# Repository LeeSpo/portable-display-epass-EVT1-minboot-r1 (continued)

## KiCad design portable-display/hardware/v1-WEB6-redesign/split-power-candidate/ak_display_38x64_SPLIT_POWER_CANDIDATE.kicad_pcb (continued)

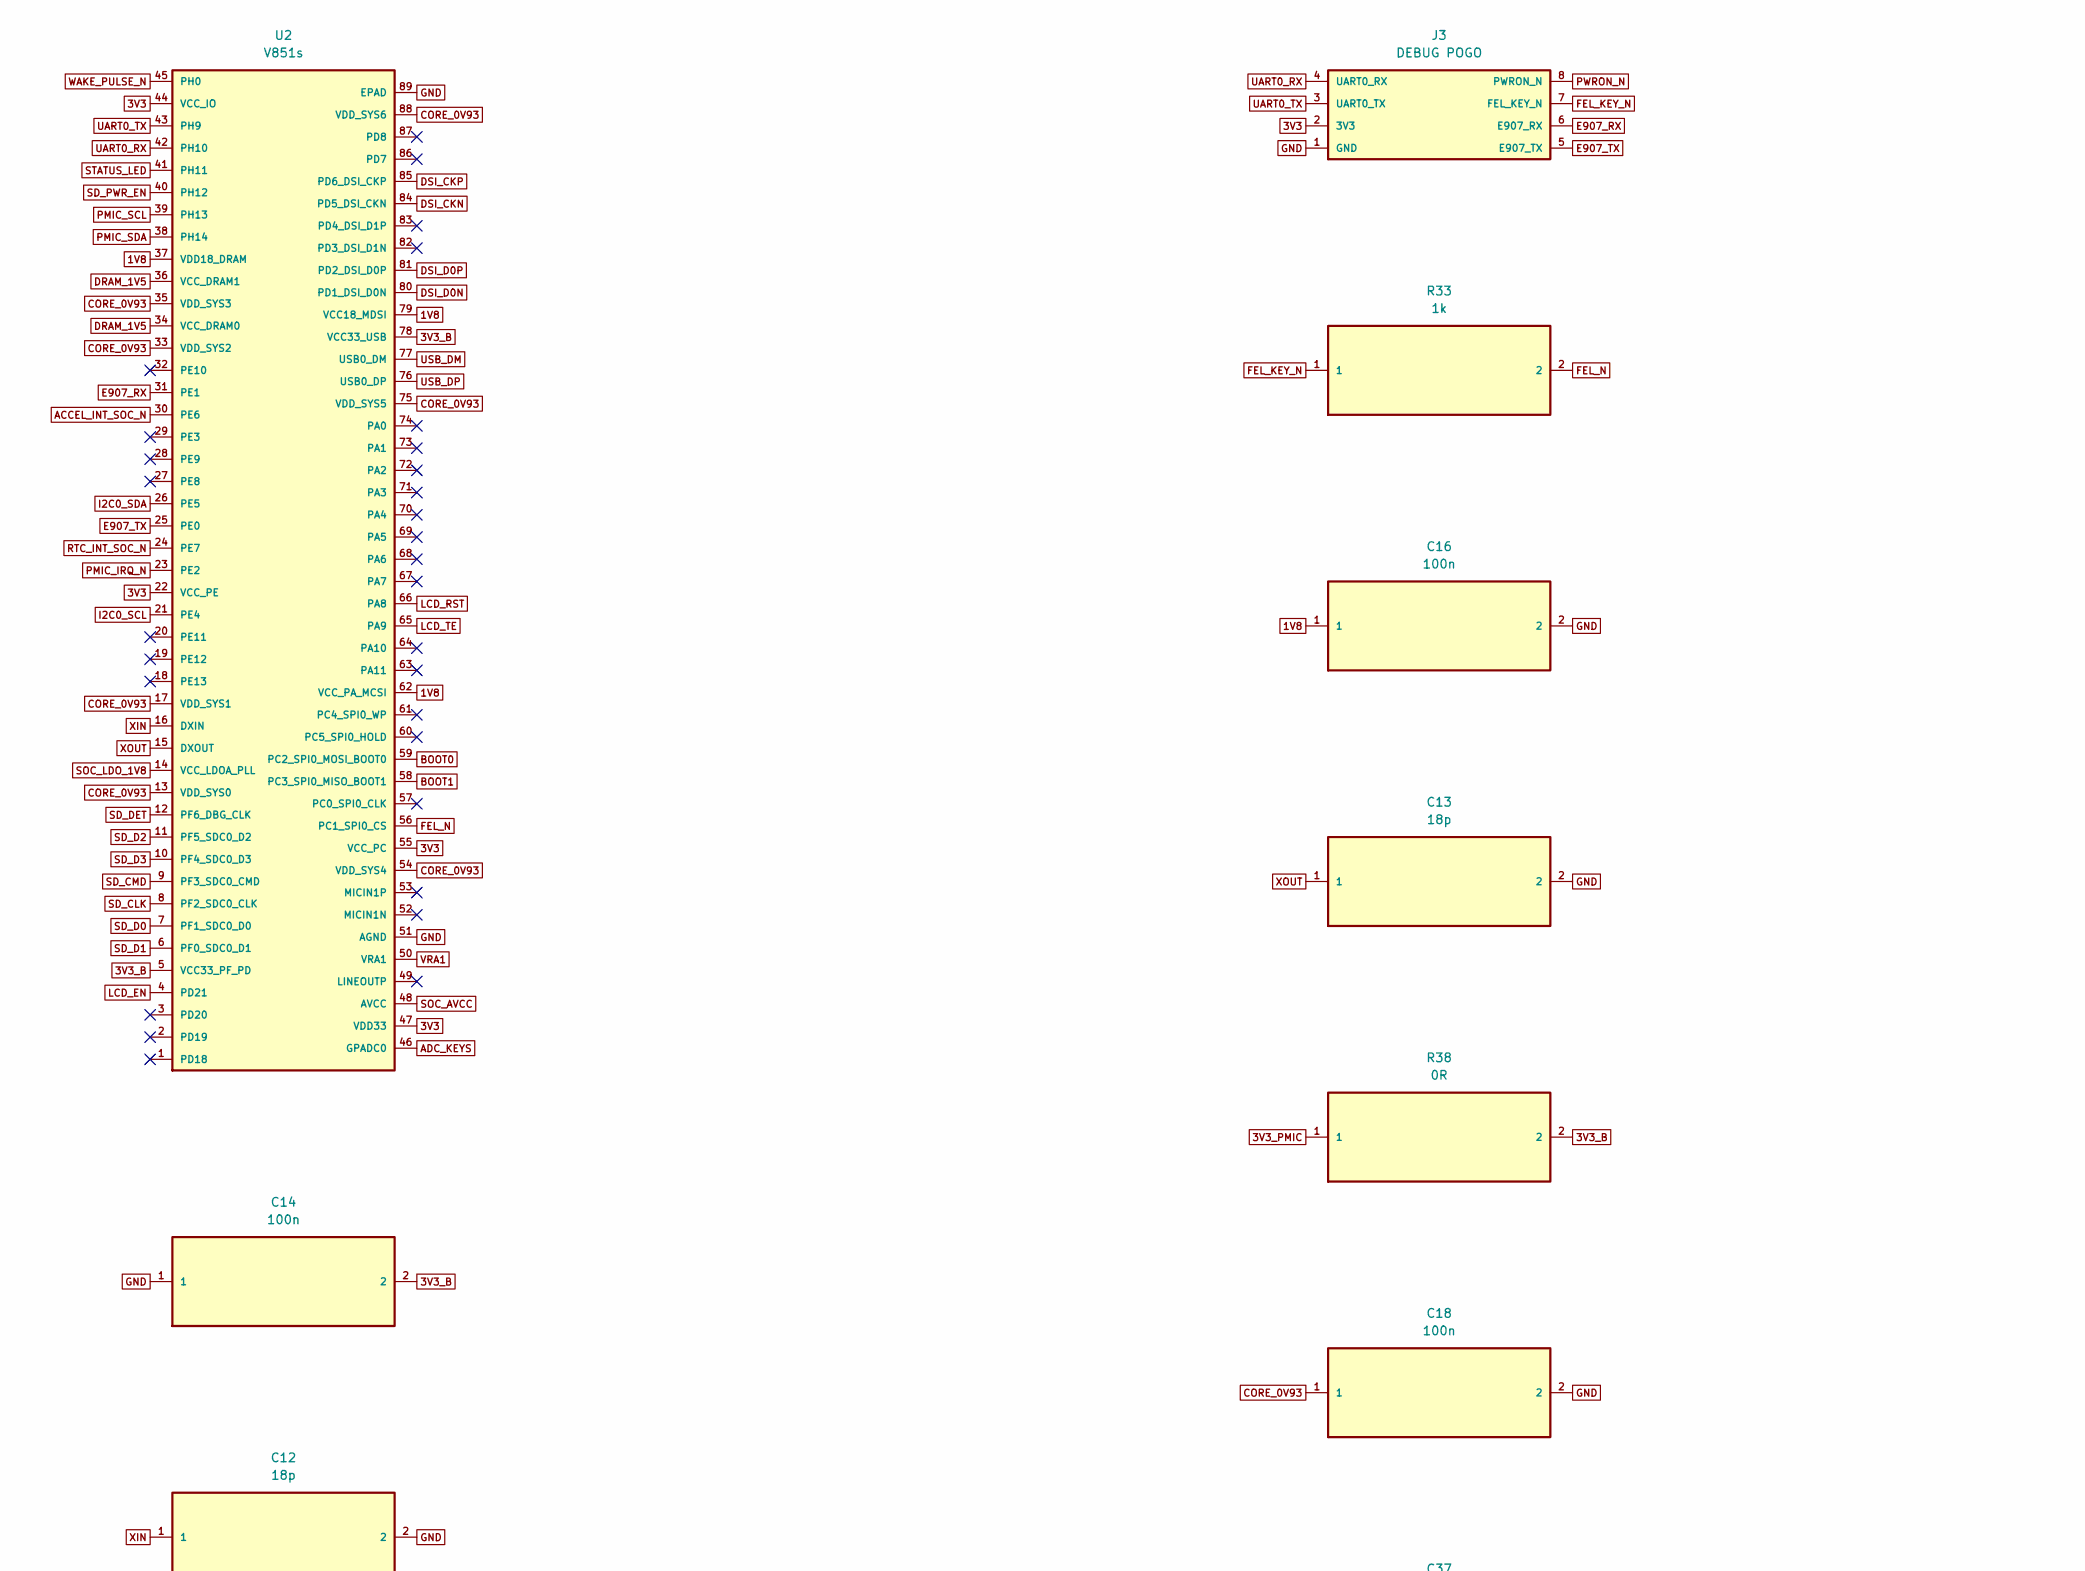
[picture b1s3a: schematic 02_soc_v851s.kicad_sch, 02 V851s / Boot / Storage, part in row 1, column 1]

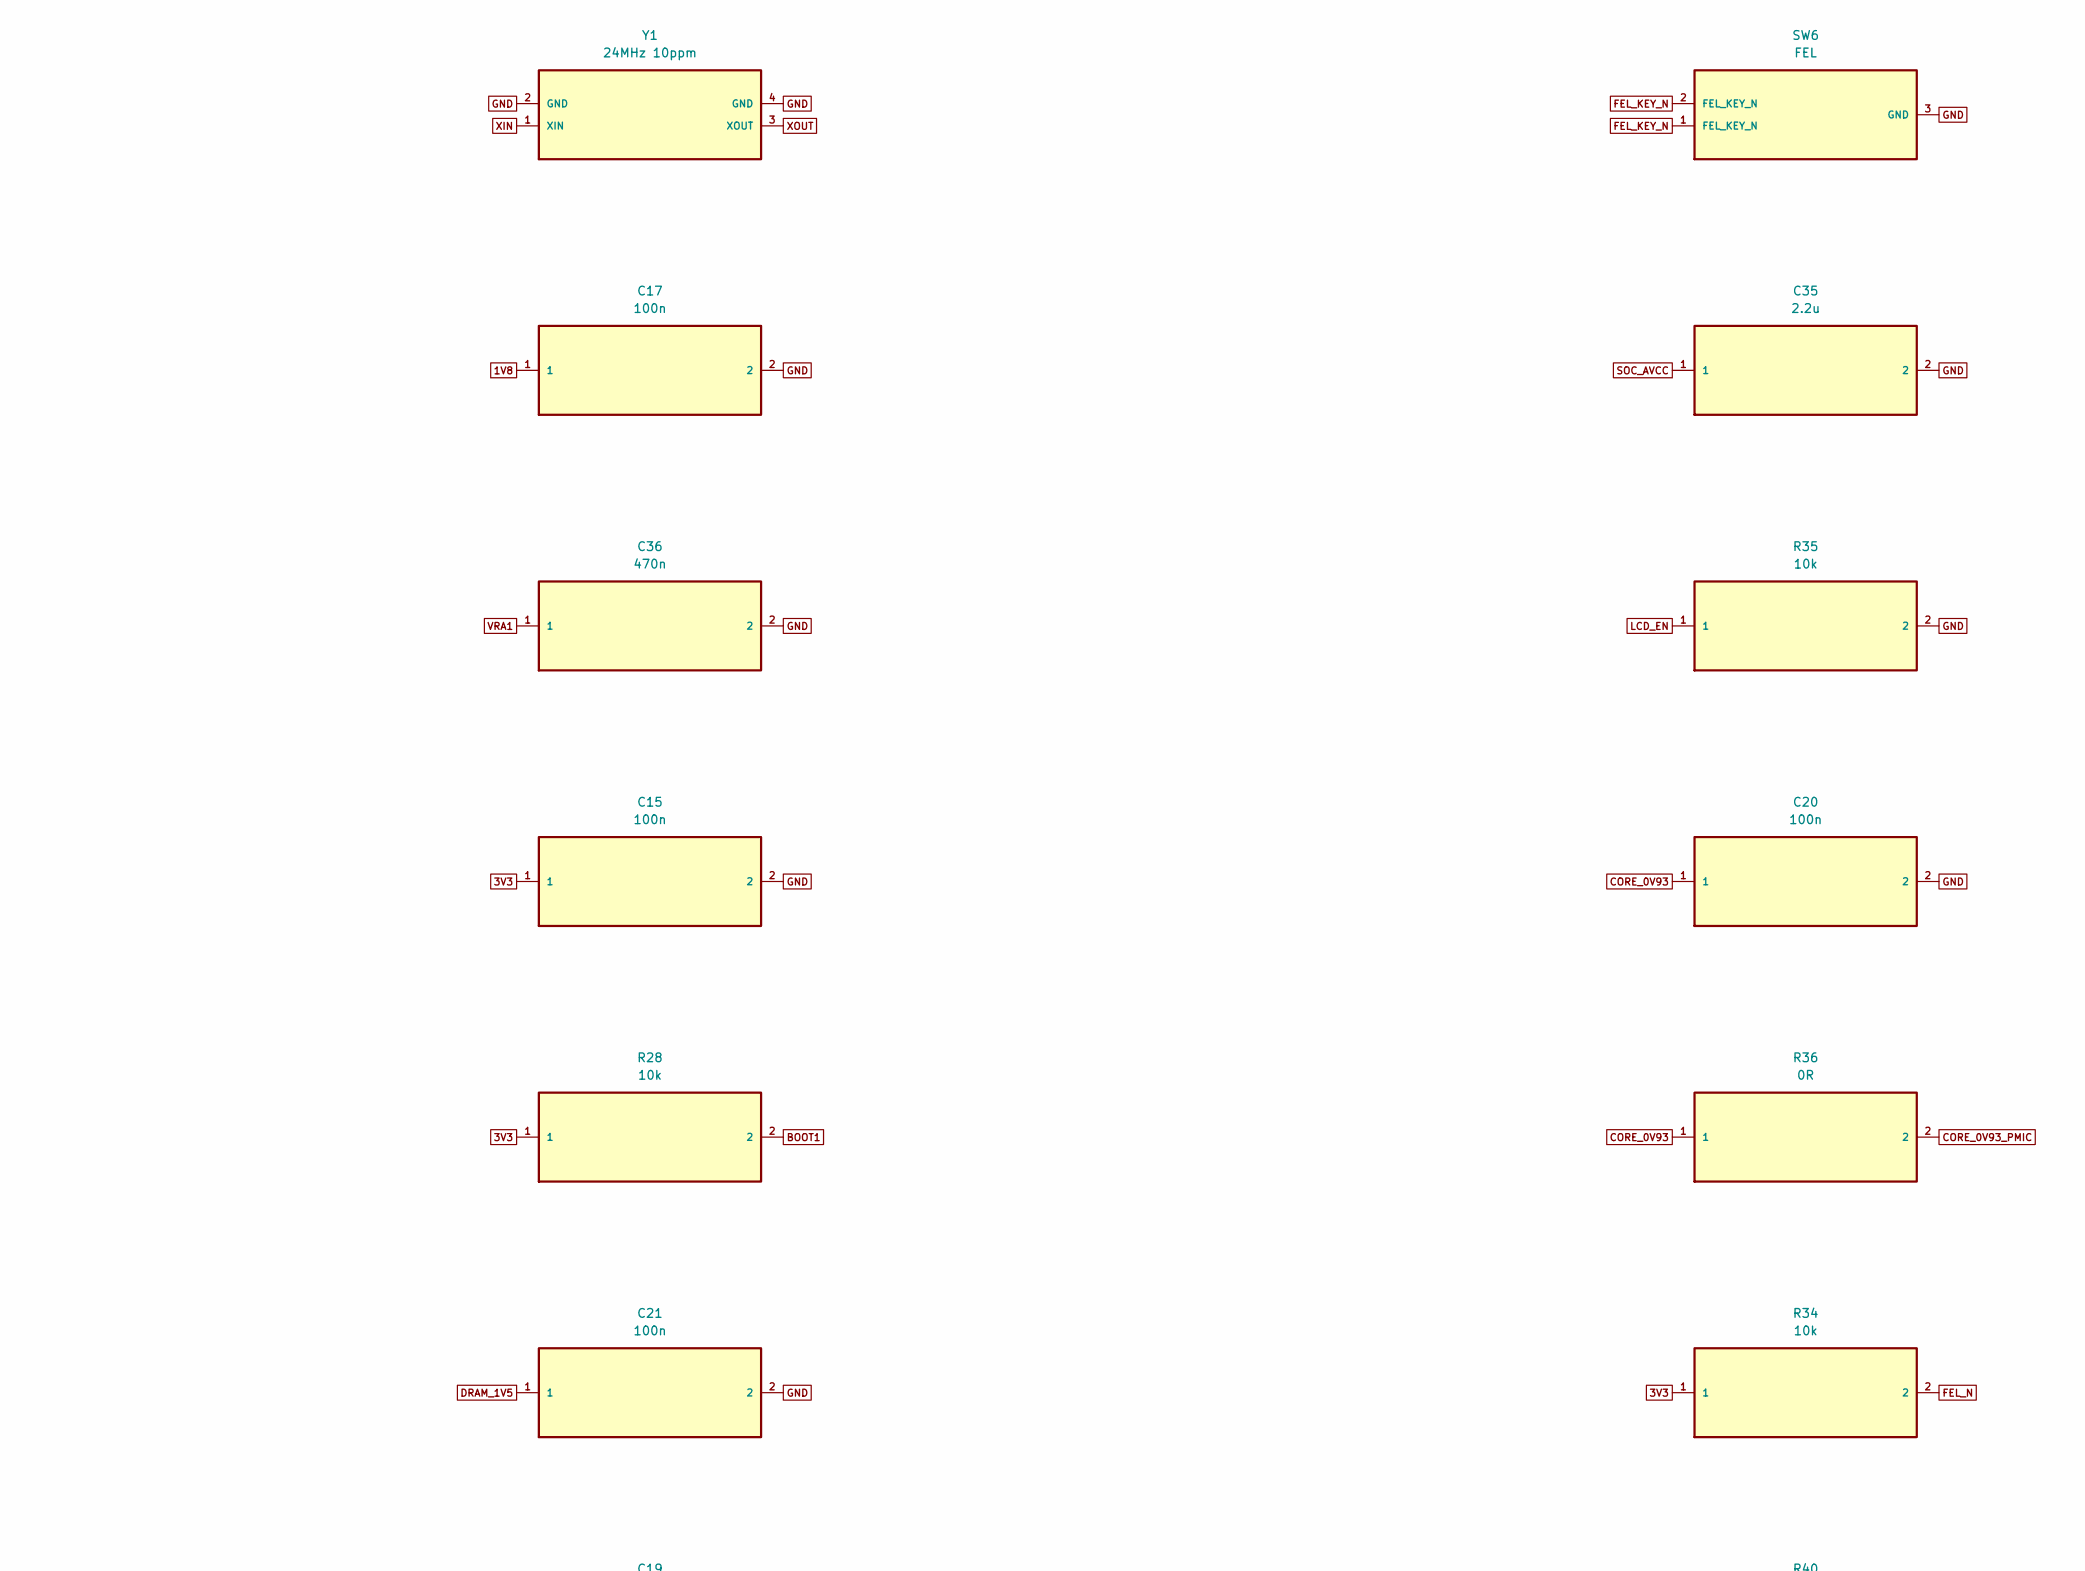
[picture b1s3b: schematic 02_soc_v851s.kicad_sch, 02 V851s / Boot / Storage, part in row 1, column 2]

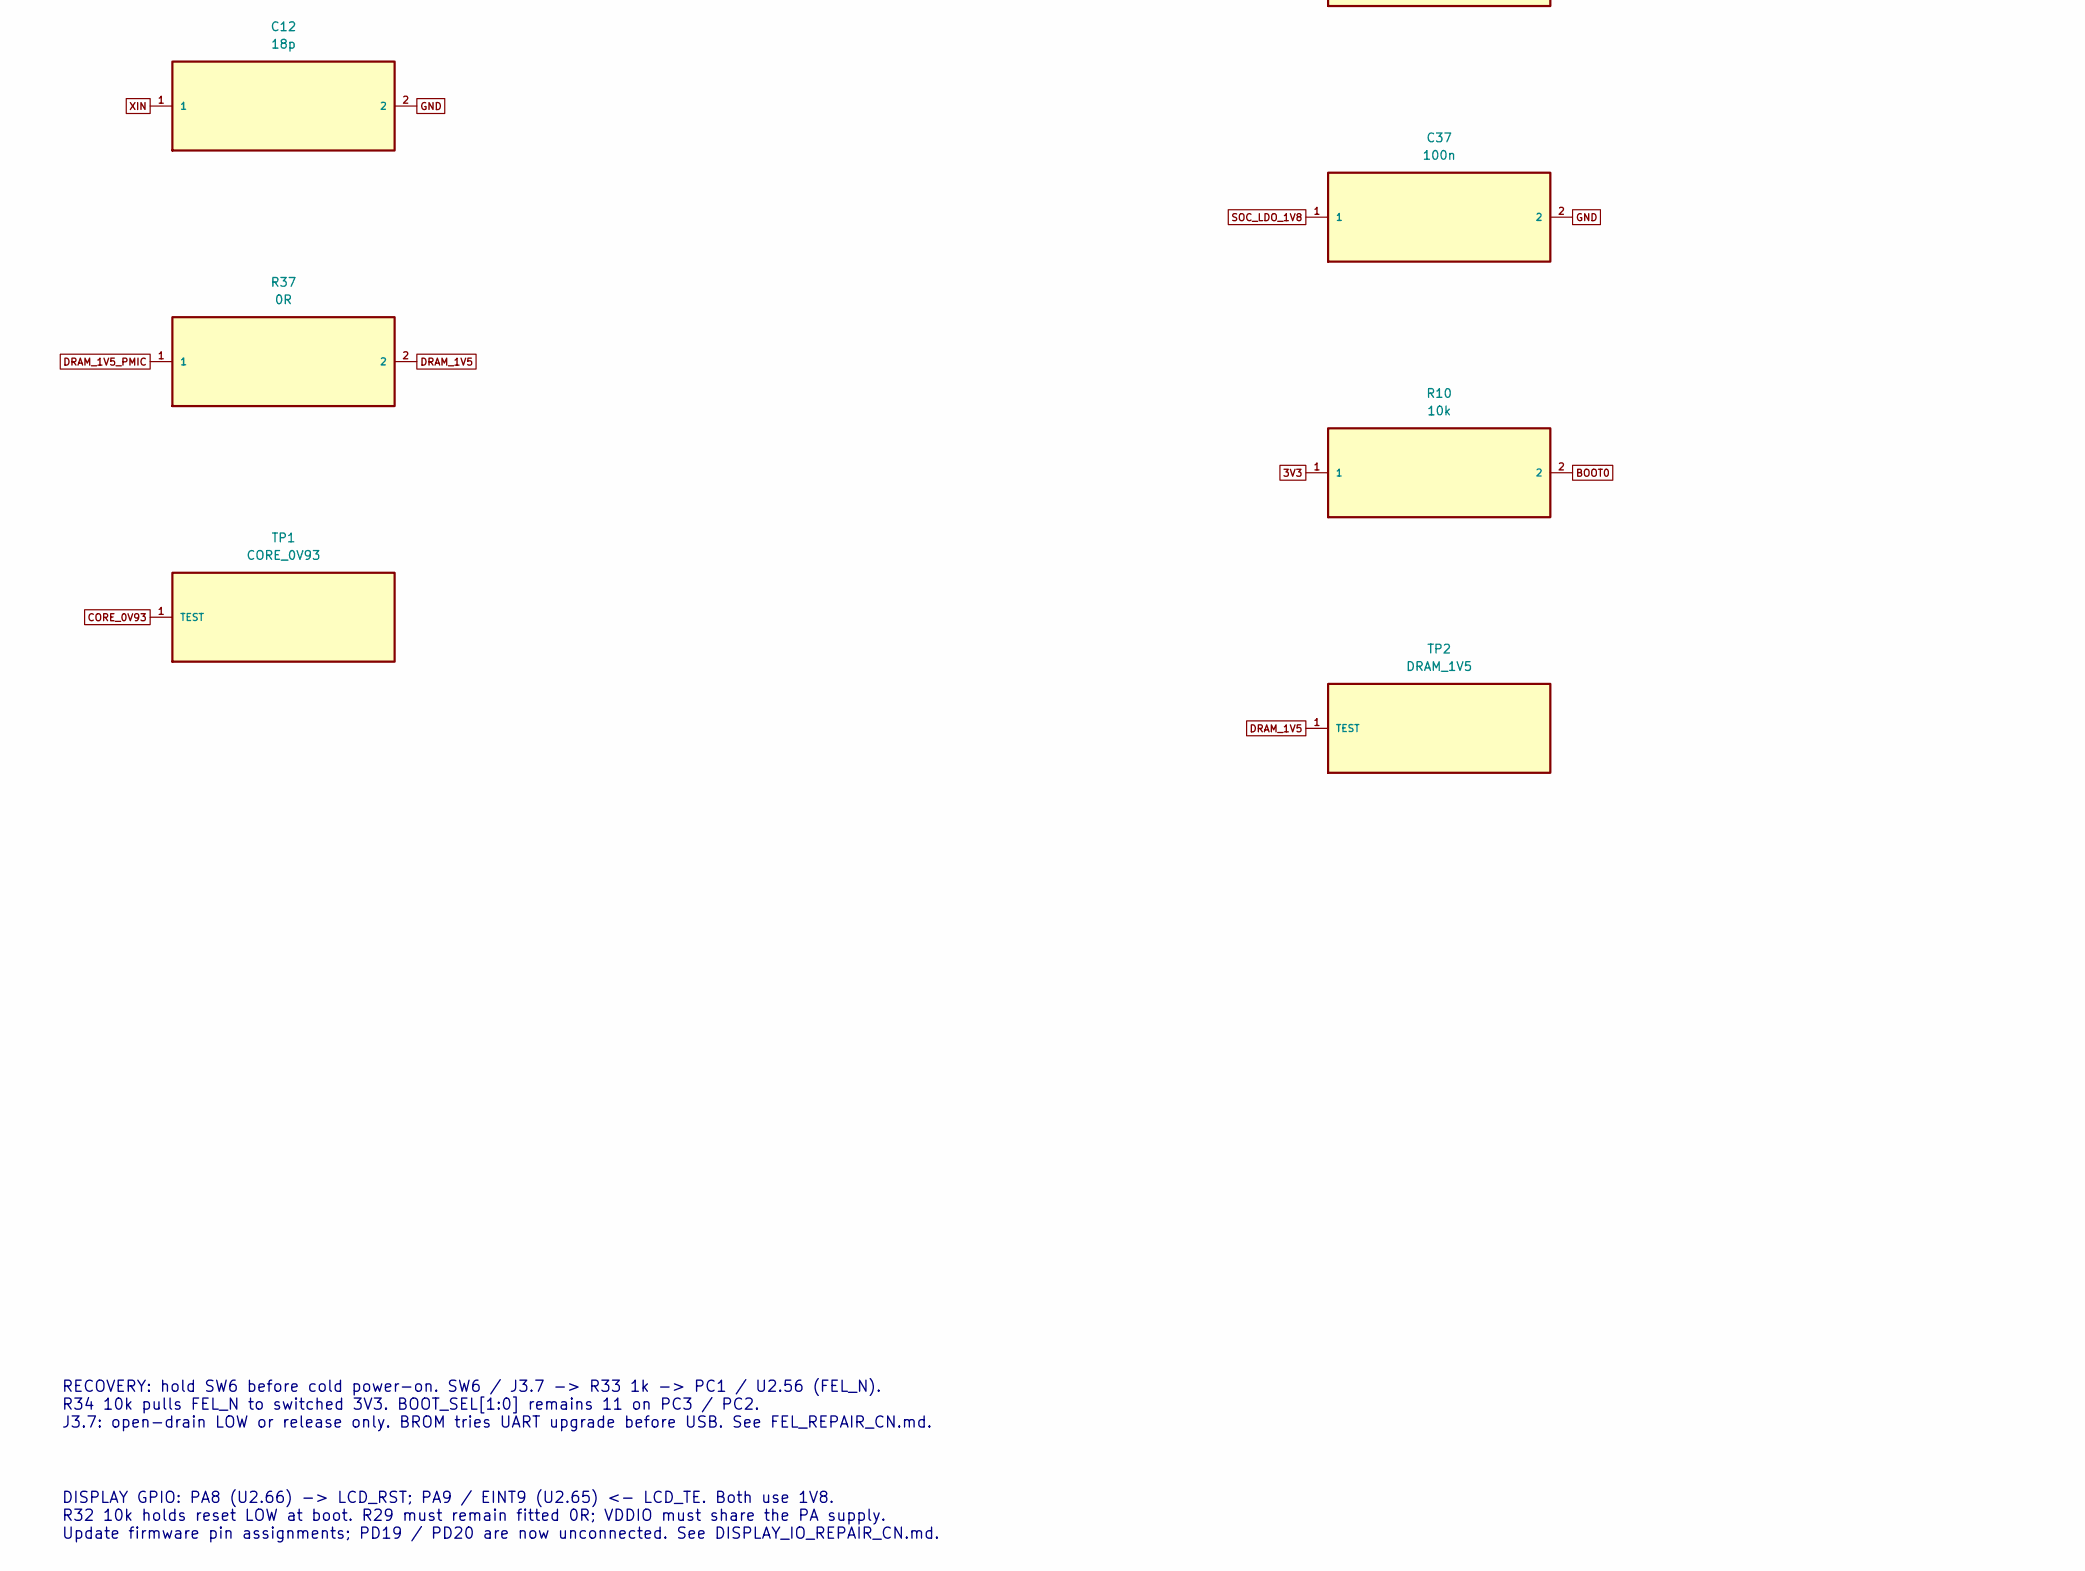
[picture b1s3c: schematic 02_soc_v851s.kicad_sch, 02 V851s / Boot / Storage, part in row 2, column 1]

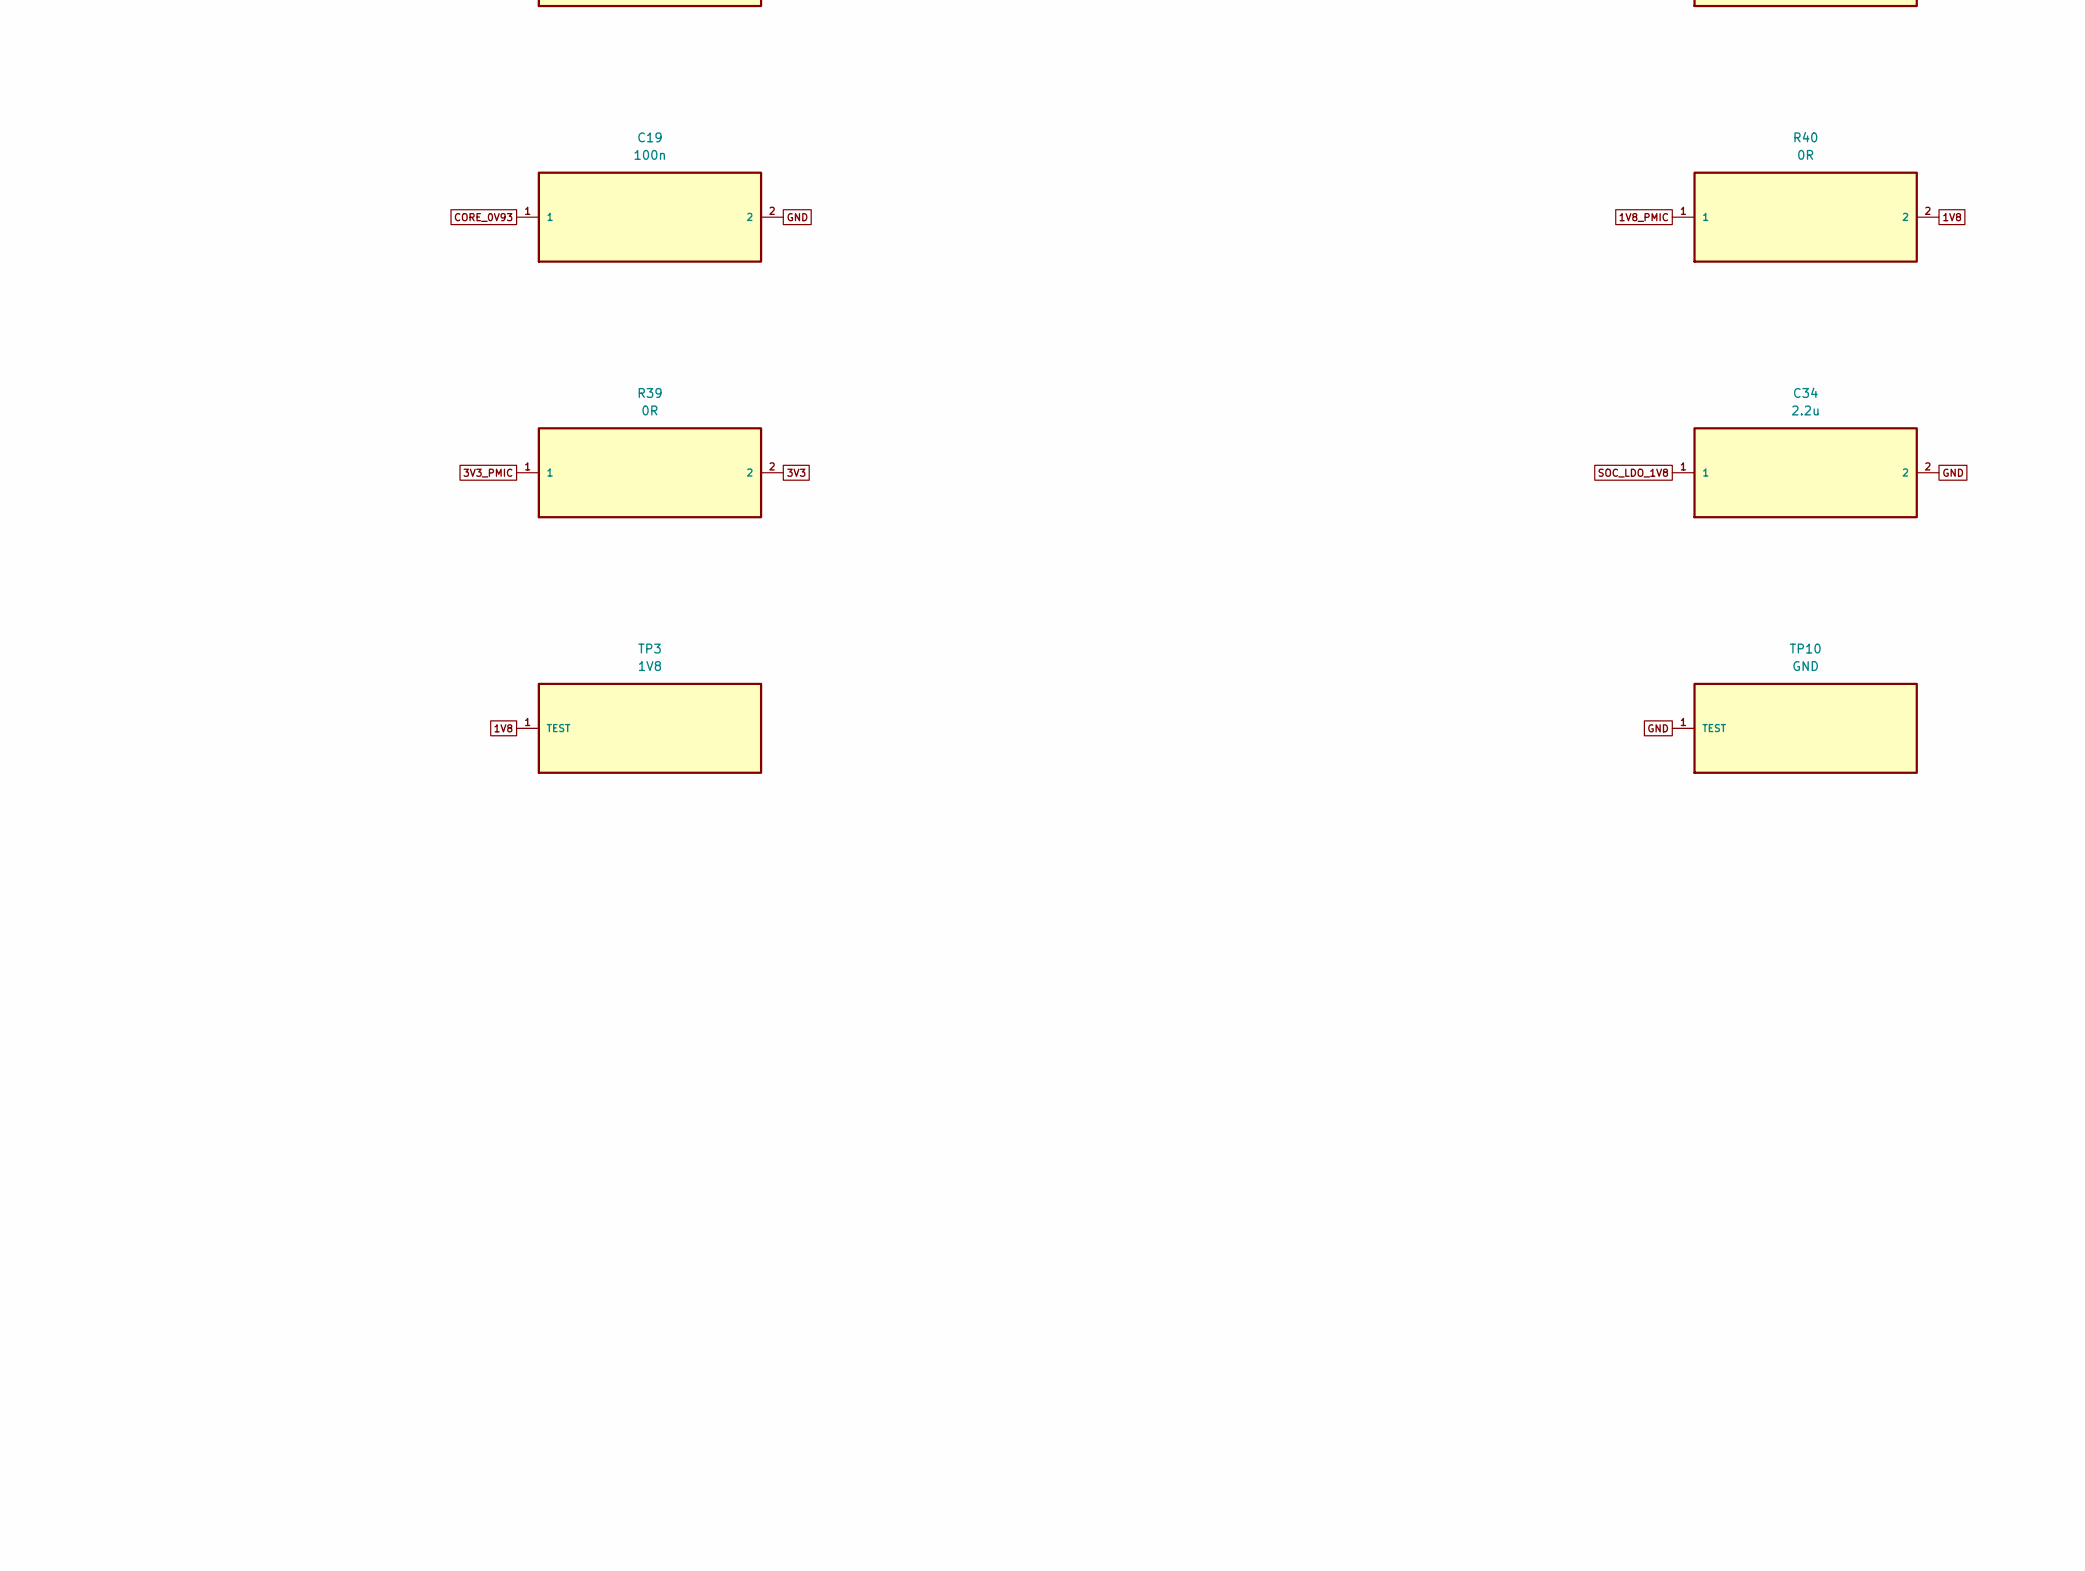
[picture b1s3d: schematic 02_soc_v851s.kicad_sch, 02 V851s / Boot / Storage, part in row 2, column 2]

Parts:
C12, C13: 18p; 0402; MPN 0402CG180J500NT; LCSC C1549
C14, C37: 100n; 0402; MPN CL05B104KO5NNNC; LCSC C1525
C15, C16, C17, C18, C19, C20, C21: 100n; 0402; MPN 0402 100n X7R; LCSC C1525
C34: 2.2u; 0402; MPN CL05A225MQ5NSNC; LCSC C12530
C35: 2.2u; 0603; MPN CL10A225KO8NNNC; LCSC C23630
C36: 470n; 0402; MPN CL05A474KP5NNNC; LCSC C47339
J3: DEBUG POGO; HDR8
R10, R28, R34, R35: 10k; 0402; MPN 0402WGF1002TCE; LCSC C25744
R33: 1k; 0402; MPN 0402WGF1001TCE; LCSC C11702
R36, R37, R38, R39, R40: 0R; 0402; MPN 0402WGF0000TCE; LCSC C17168
SW6: FEL; SW_SIDE; MPN GT-TC072B-H045-L1; LCSC C5117859
TP1: CORE_0V93; TestPoint_Pad_D1.0mm
TP2: DRAM_1V5; TestPoint_Pad_D1.0mm
TP3: 1V8; TestPoint_Pad_D1.0mm
TP10: GND; TestPoint_Pad_D1.0mm
U2: V851s; QFN88; MPN V851s; LCSC C5365286
Y1: 24MHz 10ppm; XTAL4; MPN XXDBBCNANF-24MHZ; LCSC C16197264

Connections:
1V8: C16.1, C17.1, R40.2, TP3.1 (TEST), U2.37 (VDD18_DRAM), U2.62 (VCC_PA_MCSI), U2.79 (VCC18_MDSI); also elsewhere on the board
1V8_PMIC: R40.1; also elsewhere on the board
3V3: C15.1, J3.2 (3V3), R10.1, R28.1, R34.1, R39.2, U2.22 (VCC_PE), U2.44 (VCC_IO), U2.47 (VDD33), U2.55 (VCC_PC); also elsewhere on the board
3V3_B: C14.2, R38.2, U2.5 (VCC33_PF_PD), U2.78 (VCC33_USB); also elsewhere on the board
3V3_PMIC: R38.1, R39.1; also elsewhere on the board
ACCEL_INT_SOC_N: U2.30 (PE6); also elsewhere on the board
ADC_KEYS: U2.46 (GPADC0); also elsewhere on the board
BOOT0: R10.2, U2.59 (PC2_SPI0_MOSI_BOOT0)
BOOT1: R28.2, U2.58 (PC3_SPI0_MISO_BOOT1)
CORE_0V93: C18.1, C19.1, C20.1, R36.1, TP1.1 (TEST), U2.13 (VDD_SYS0), U2.17 (VDD_SYS1), U2.33 (VDD_SYS2), U2.35 (VDD_SYS3), U2.54 (VDD_SYS4), U2.75 (VDD_SYS5), U2.88 (VDD_SYS6); also elsewhere on the board
CORE_0V93_PMIC: R36.2; also elsewhere on the board
DRAM_1V5: C21.1, R37.2, TP2.1 (TEST), U2.34 (VCC_DRAM0), U2.36 (VCC_DRAM1)
DRAM_1V5_PMIC: R37.1; also elsewhere on the board
DSI_CKN: U2.84 (PD5_DSI_CKN); also elsewhere on the board
DSI_CKP: U2.85 (PD6_DSI_CKP); also elsewhere on the board
DSI_D0N: U2.80 (PD1_DSI_D0N); also elsewhere on the board
DSI_D0P: U2.81 (PD2_DSI_D0P); also elsewhere on the board
E907_RX: J3.6 (E907_RX), U2.31 (PE1)
E907_TX: J3.5 (E907_TX), U2.25 (PE0)
FEL_KEY_N: J3.7 (FEL_KEY_N), R33.1, SW6.1 (FEL_KEY_N), SW6.2 (FEL_KEY_N)
FEL_N: R33.2, R34.2, U2.56 (PC1_SPI0_CS)
GND: C12.2, C13.2, C14.1, C15.2, C16.2, C17.2, C18.2, C19.2, C20.2, C21.2, C34.2, C35.2, C36.2, C37.2, J3.1 (GND), R35.2, SW6.3 (GND), TP10.1 (TEST), U2.51 (AGND), U2.89 (EPAD), Y1.2 (GND), Y1.4 (GND); also elsewhere on the board
I2C0_SCL: U2.21 (PE4); also elsewhere on the board
I2C0_SDA: U2.26 (PE5); also elsewhere on the board
LCD_EN: R35.1, U2.4 (PD21); also elsewhere on the board
LCD_RST: U2.66 (PA8); also elsewhere on the board
LCD_TE: U2.65 (PA9); also elsewhere on the board
PMIC_IRQ_N: U2.23 (PE2); also elsewhere on the board
PMIC_SCL: U2.39 (PH13); also elsewhere on the board
PMIC_SDA: U2.38 (PH14); also elsewhere on the board
PWRON_N: J3.8 (PWRON_N); also elsewhere on the board
RTC_INT_SOC_N: U2.24 (PE7); also elsewhere on the board
SD_CLK: U2.8 (PF2_SDC0_CLK); also elsewhere on the board
SD_CMD: U2.9 (PF3_SDC0_CMD); also elsewhere on the board
SD_D0: U2.7 (PF1_SDC0_D0); also elsewhere on the board
SD_D1: U2.6 (PF0_SDC0_D1); also elsewhere on the board
SD_D2: U2.11 (PF5_SDC0_D2); also elsewhere on the board
SD_D3: U2.10 (PF4_SDC0_D3); also elsewhere on the board
SD_DET: U2.12 (PF6_DBG_CLK); also elsewhere on the board
SD_PWR_EN: U2.40 (PH12); also elsewhere on the board
SOC_AVCC: C35.1, U2.48 (AVCC)
SOC_LDO_1V8: C34.1, C37.1, U2.14 (VCC_LDOA_PLL)
STATUS_LED: U2.41 (PH11); also elsewhere on the board
UART0_RX: J3.4 (UART0_RX), U2.42 (PH10)
UART0_TX: J3.3 (UART0_TX), U2.43 (PH9)
USB_DM: U2.77 (USB0_DM); also elsewhere on the board
USB_DP: U2.76 (USB0_DP); also elsewhere on the board
VRA1: C36.1, U2.50 (VRA1)
WAKE_PULSE_N: U2.45 (PH0); also elsewhere on the board
XIN: C12.1, U2.16 (DXIN), Y1.1 (XIN)
XOUT: C13.1, U2.15 (DXOUT), Y1.3 (XOUT)

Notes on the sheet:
RECOVERY: hold SW6 before cold power-on. SW6 / J3.7 -> R33 1k -> PC1 / U2.56 (FEL_N). R34 10k pulls FEL_N to switched 3V3. BOOT_SEL[1:0] remains 11 on PC3 / PC2. J3.7: open-drain LOW or release only. BROM tries UART upgrade before USB. See FEL_REPAIR_CN.md.
DISPLAY GPIO: PA8 (U2.66) -> LCD_RST; PA9 / EINT9 (U2.65) <- LCD_TE. Both use 1V8. R32 10k holds reset LOW at boot. R29 must remain fitted 0R; VDDIO must share the PA supply. Update firmware pin assignments; PD19 / PD20 are now unconnected. See DISPLAY_IO_REPAIR_CN.md.
